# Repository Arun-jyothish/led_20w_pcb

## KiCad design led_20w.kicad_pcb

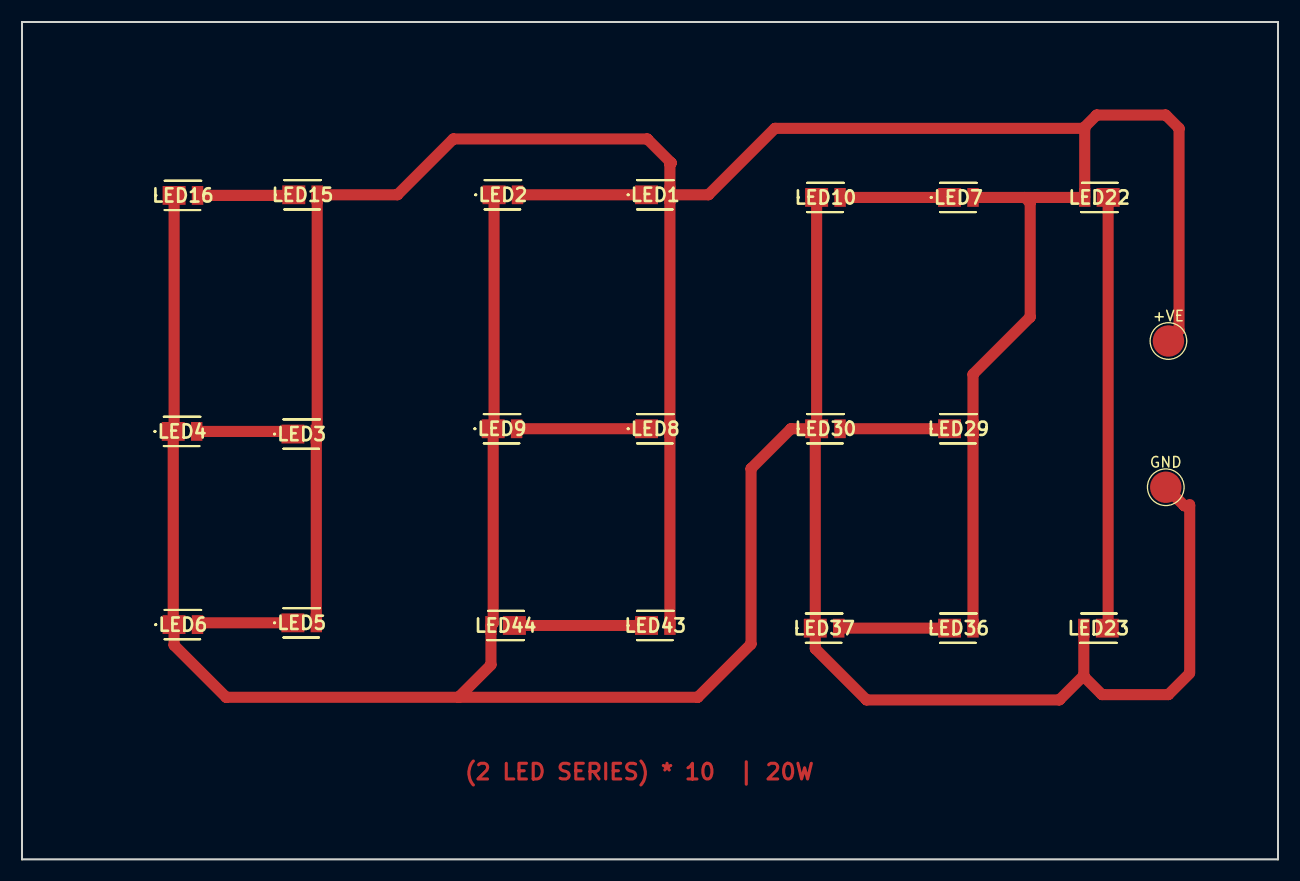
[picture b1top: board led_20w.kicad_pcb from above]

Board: 2 copper layers, 120.0 x 80.0 mm, 22 parts (0 on the bottom side), 12 nets.

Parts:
+VE: TestPoint; TestPoint_Pad_D3.0mm
GND: TestPoint; TestPoint_Pad_D3.0mm
LED1, LED2, LED3, LED4, LED5, LED6, LED7, LED8, LED9, LED10, LED15, LED16, LED22, LED23, LED29, LED30, LED36, LED37, LED43, LED44: JB2835BWT-G-H40EA0000-N0000001; JB2835BWTGH40EA0000N0000001

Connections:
+24V: +VE.1, LED1.2, LED3.2, LED5.2, LED7.2, LED8.2, LED15.2, LED22.2, LED29.2, LED36.2, LED43.2
GND: GND.1, LED2.1, LED4.1, LED6.1, LED9.1, LED10.1, LED16.1, LED23.2, LED30.1, LED37.1, LED44.2
unnamed: LED1.1, LED2.2
unnamed: LED3.1, LED4.2
unnamed: LED5.1, LED6.2
unnamed: LED8.1, LED9.2
unnamed: LED7.1, LED10.2
unnamed: LED15.1, LED16.2
unnamed: LED22.1, LED23.1
unnamed: LED29.1, LED30.2
unnamed: LED36.1, LED37.2
unnamed: LED43.1, LED44.1

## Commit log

2022-04-23 finalized
2022-04-24 60W gbr 3d pdf
